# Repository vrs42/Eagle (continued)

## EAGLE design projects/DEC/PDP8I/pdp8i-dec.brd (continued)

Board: 2 copper layers, 330 parts (0 on the bottom side), 1704 nets, no tracks yet.

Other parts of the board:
U$1, U$2, U$3, U$4, U$5, U$6, U$7, U$8, U$9, U$10, U$11, U$12, U$13, U$14, U$15, U$16, U$17, U$18, U$19, U$20, U$21, U$22, U$23, U$24, U$25, U$26, U$27, U$28, U$29, U$30, U$31, U$32, U$33, U$34, U$35, U$36, U$37, U$38, U$39, U$40: CBLOCK

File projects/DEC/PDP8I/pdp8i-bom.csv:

"Qty";"Value";"Device";"Package";"Parts";"Description";"";
"2";"A607";"A607";"H807-2";"HJ24, HJ25";"A607 Digital to Analog Converter";"";
"28";"EMPTY";"EMPTY";"H807";"E03, E04, E05, E06, E07, E08, F04, F05, F06, F07, H06, H21, H22, H33, H35, H36, H37, H38, H39, H40, J21, J22, J35, J36, J37, J38, J39, J40";"Empty Slot";"";
"7";"G021";"G021";"H807";"A30, A31, A32, A33, B31, B32, B33";"Sense Amps";"";
"16";"G221";"G221";"H807";"C25, C26, C30, C31, C32, C33, C37, C38, D25, D26, D30, D31, D32, D33, D37, D38";"Memory Selector";"";
"9";"G228";"G228";"H807";"A27, A36, A37, B26, B27, B36, B37, C39, D39";"Inhibit Driver";"";
"2";"G610";"G610";"H807-2";"CD27, CD34";"G610 Core Connector";"";
"2";"G611";"G610";"H807-2";"CD29, CD36";"G610 Core Connector";"";
"7";"G624";"G624";"H807";"A25, A26, A38, A39, B25, B38, B39";"Resistor Board";"";
"1";"G792";"G792";"H807-2";"AB03";"Power Supply Connector";"";
"1";"G805";"G805";"H807-2";"AB01";"Negative Regulator";"";
"1";"G826";"G826";"H807-2";"AB02";"Regulator and Power Detector";"";
"4";"H807";"H807";"H807";"C28, C35, D28, D35";"Empty card slot";"";
"5";"M040";"M040";"H807";"C02, C03, C04, C05, C06";"M040 Solenoid Driver";"";
"40";"M113";"M113";"H807";"A05, A06, A11, A12, A13, A14, A15, A16, A17, A18, A19, B06, B08, B09, B21, C09, C10, C14, C15, C16, C17, C18, D07, D12, D13, D14, D15, D16, E09, E11, E12, E15, E22, E24, F20, F21, F22, F25, F29, F32";"10 2-input NAND Gates";"";
"17";"M115";"M115";"H807";"A20, B04, B07, B20, C11, C19, C20, C21, D09, D17, D18, D19, E14, E21, E25, F26, F28";"8 3-input NAND Gates";"";
"8";"M117";"M117";"H807";"D10, D20, D21, F11, F19, F23, F24, F27";"6 4-input NAND Gates";"";
"1";"M119";"M119";"H807";"F09";"3 8-input NAND Gates";"";
"8";"M160";"M160";"H807";"D23, E13, E26, E27, E28, E29, E30, F33";"AND-NOR Gates";"";
"4";"M162";"M162";"H807";"A07, A08, A09, A10";"Parity Circuit";"";
"6";"M216";"M206X";"H807";"B22, E18, E19, E20, E23, E33";"Two sets of 3 D flip-flops";"";
"10";"M216";"M216";"H807";"B05, B11, B17, B18, B19, C22, C23, C24, D11, D24";"Two sets of 3 D flip-flops";"";
"6";"M220";"M220";"H807-2";"EF34, EF35, EF36, EF37, EF38, EF39";"PDP-8 Major Registers";"";
"16";"M310";"M310";"H807";"A21, A22, A23, A24, C13, D06, D08, E16, E17, F12, F13, F14, F15, F16, F17, F18";"Tapped Delay Line";"";
"2";"M360";"M360";"H807";"B23, B24";"Variable Delay";"";
"1";"M401/M405/M501";"M501";"H807";"J30";"M401/M405/M501 Frequency Source";"";
"1";"M452";"M452";"H807";"F03";"M452 Baud Rate Clock";"";
"8";"M506";"M506";"H807";"J13, J14, J15, J16, J17, J18, J19, J20";"Hex Negative Bus Receiver";"";
"1";"M516";"M516";"H807";"D05";"Hex Positive Bus Receiver";"";
"12";"M617";"M617";"H807";"B12, B13, B14, B15, B16, B30, C12, D22, E31, E32, F30, F31";"6 4-input NAND Buffers";"";
"14";"M650";"M650";"H807";"H07, H08, H09, H10, H11, H12, H13, H14, H15, H16, H17, H18, H19, H20";"";"";
"2";"M660";"M660";"H807";"C08, F08";"Positive Level Driver";"";
"1";"M661";"M661";"H807";"C07";"Positive Level Driver";"";
"1";"M700";"M700";"H807-2";"EF10";"Manual Function Timing and Run";"";
"1";"M701";"M701";"H807-2";"HJ23";"M701 Display Control";"";
"1";"M703";"M703";"H807";"A04";"M703 Power Fail and Restart";"";
"1";"M704";"M704";"H807-2";"HJ29";"M704 Plotter Control";"";
"1";"M705";"M705";"H807-2";"HJ26";"Reader Control";"";
"1";"M706";"M706";"H807-2";"EF01";"M706 TTY Receiver";"";
"1";"M707";"M707";"H807-2";"EF02";"M707 TTY Transmitter";"";
"1";"M708";"M708";"H807";"H30";"M708 Clock Control";"";
"1";"M709";"M709";"H807-2";"HJ31";"M709 Clock Counter";"";
"1";"M710";"M710";"H807-2";"HJ28";"Punch Control";"";
"1";"M714";"M714";"H807";"J33";"M714 Card Reader Control";"";
"1";"M715";"M715";"H807-2";"HJ27";"Reader Clock";"";
"1";"M716";"M716";"H807-2";"HJ32";"M716 Card Reader Control";"";
"1";"M720";"M720";"H807";"B10";"M720 Memory Detection";"";
"4";"M900";"M916";"H807";"C40, D40, E40, F40";"Simple 36 pin connector/wire cable";"";
"17";"W011";"W011";"H807";"D04, H01, H02, H03, H04, H05, J01, J02, J03, J04, J05, J06, J07, J08, J09, J10, J11";"One-sided 9 pin connector/cable with grounds (Negibus).";"";
"3";"W023";"W023";"H807";"C01, D02, D03";"One-sided 18 pin connector/cable.";"";
"4";"W025";"W025";"H807-2";"AB28, AB29, AB34, AB35";"Core memory cable.";"";
"1";"W076";"W076";"H807";"J12";"W076 Terminal Connector";"";
"2";"W077";"M916";"H807";"A40, B40";"Simple 36 pin connector/wire cable";"";
"1";"W077";"W023";"H807";"D01";"One-sided 18 pin connector/cable.";"";
"1";"W991";"W991";"H807-2";"HJ34";"One-sided 36 pin (double hight) connector/cable.";"";

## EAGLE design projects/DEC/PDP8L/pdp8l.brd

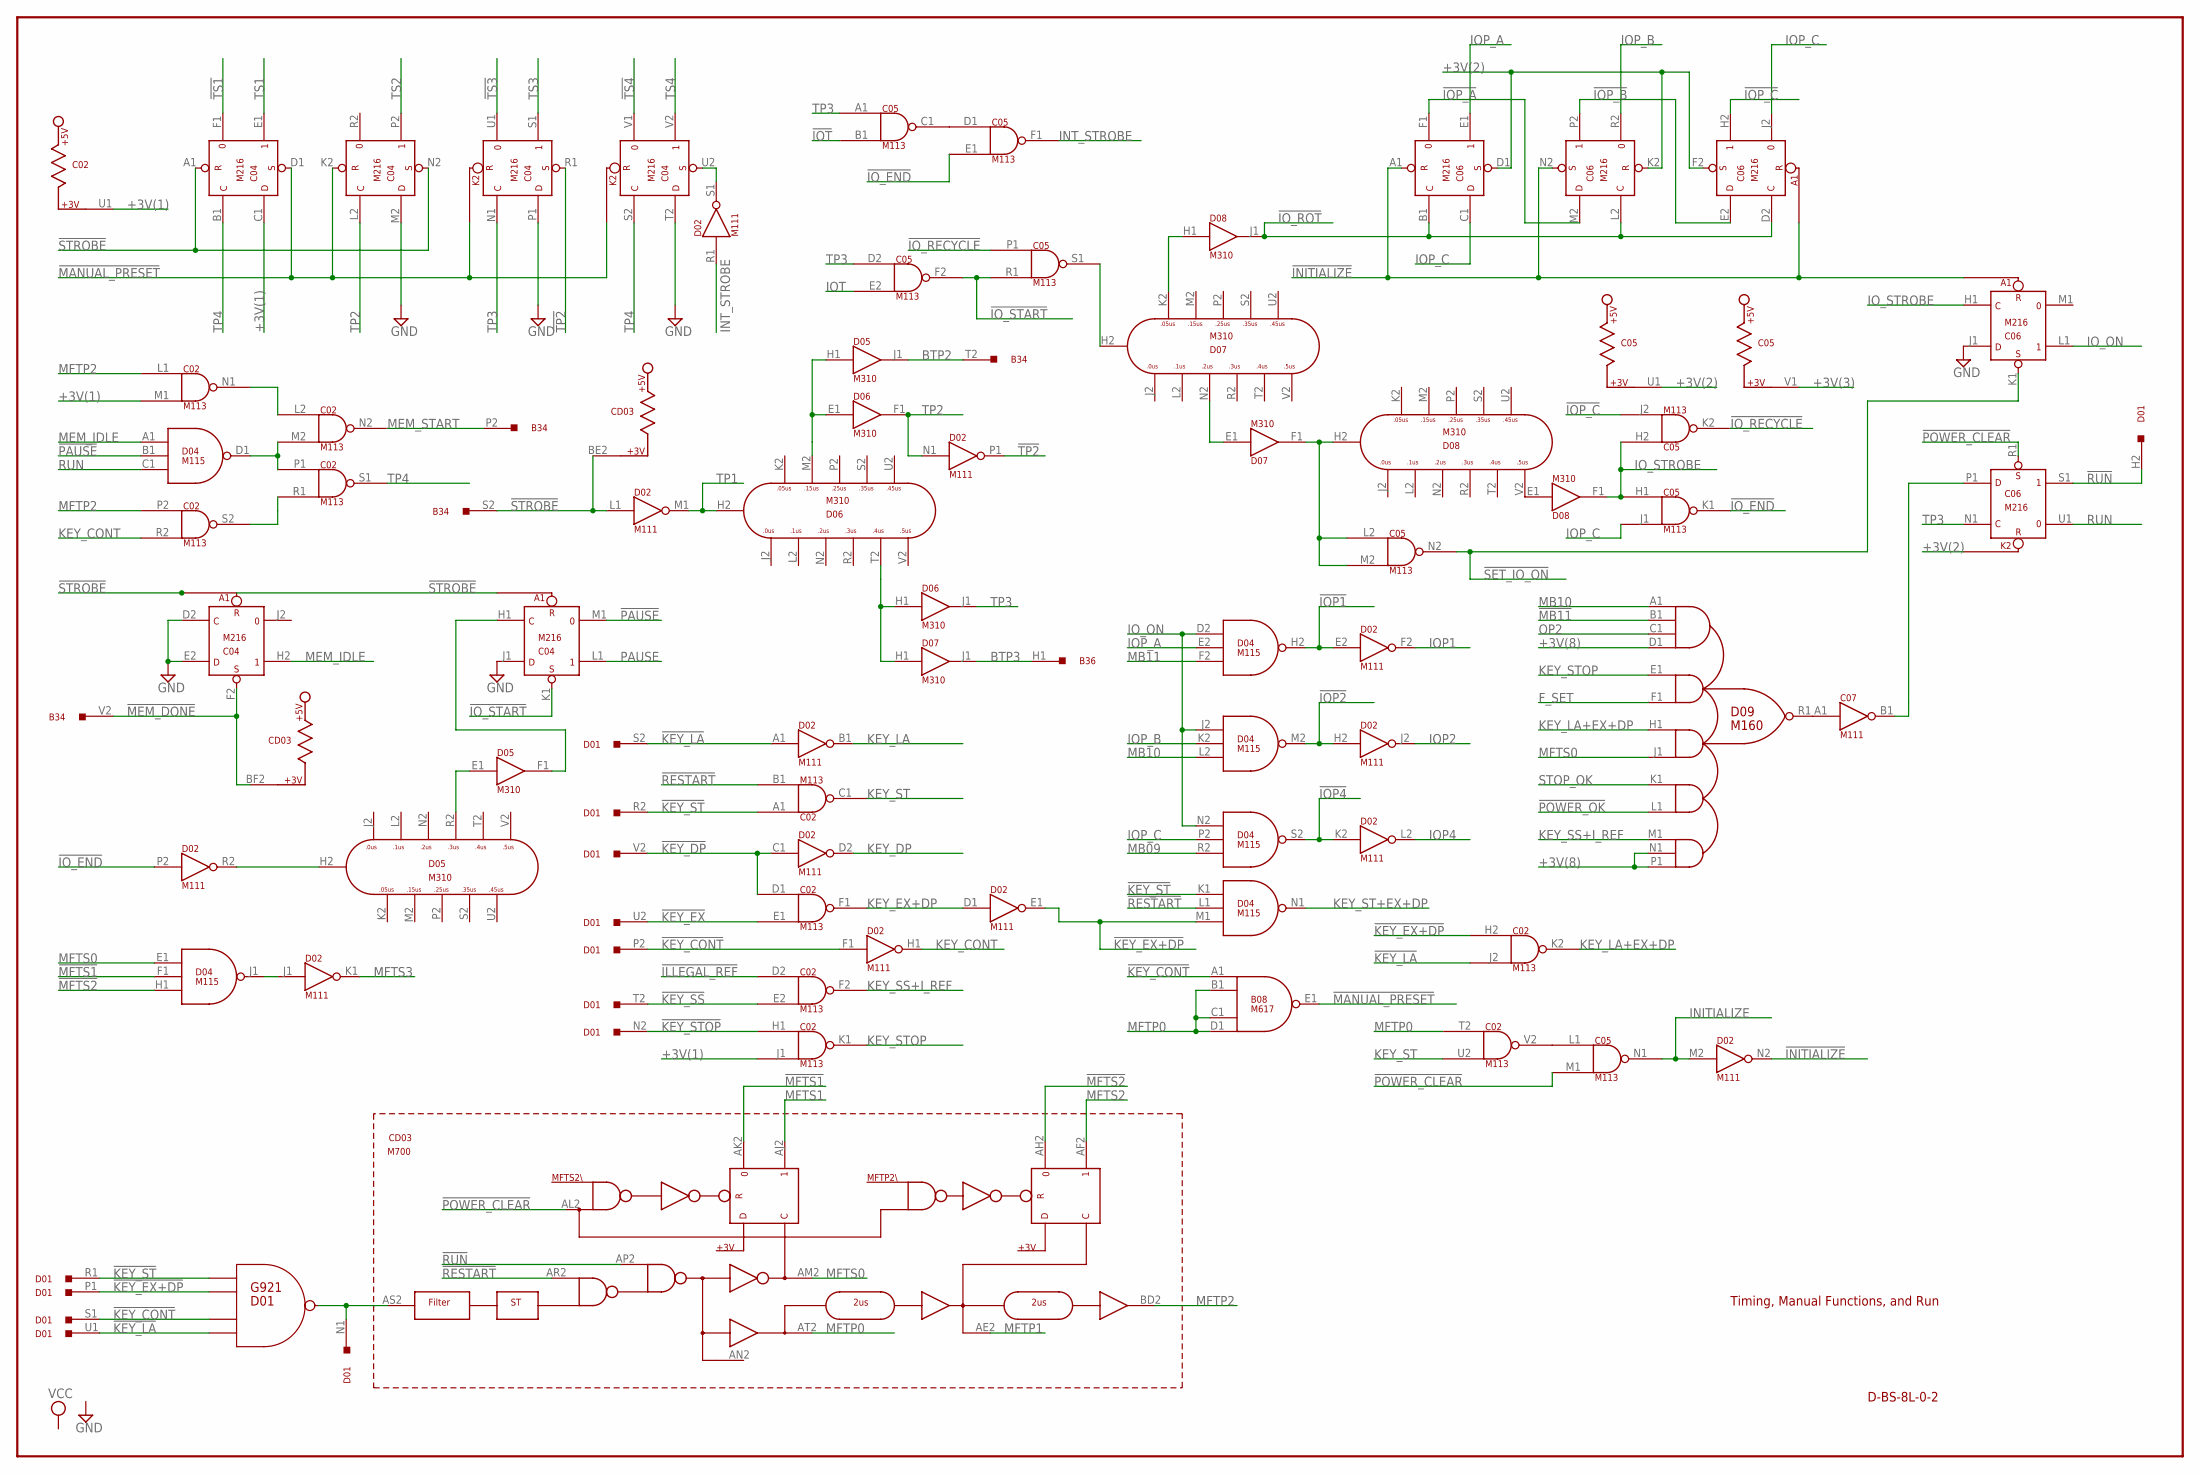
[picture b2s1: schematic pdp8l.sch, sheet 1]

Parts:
B08: M617; H807
B34, B36: M903; H807
C02, C05: M113; H807
C04, C06: M216; H807
C07: M111; H807
CD03: M700; H807-2
D01: G921; H807
D02: M111; H807
D04: M115; H807
D05, D06, D07, D08: M310; H807
D09: M160; H807

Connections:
!ILLEGAL_REF: C02.D2 (IN1); also elsewhere on the board
!INITIALIZE: C06.A1 (R), C06.N2 (S), D02.N2 (OUT); also elsewhere on the board
!INT_STROBE: C04.U2 (S), D02.S1 (OUT)
!IOP1: D02.E2 (IN), D04.H2 (OUT); also elsewhere on the board
!IOP2: D02.H2 (IN), D04.M2 (OUT); also elsewhere on the board
!IOP4: D02.K2 (IN), D04.S2 (OUT); also elsewhere on the board
!IOP_A: C06.F1 (0), C06.M2 (D)
!IOP_B: C06.E2 (D), C06.P2 (1)
!IOP_C: C05.J2 (IN2), C06.H2 (1)
!IOT: C05.B1 (IN2); also elsewhere on the board
!IO_END: C05.E1 (IN2), C05.K1 (OUT), D02.P2 (IN)
!IO_RECYCLE: C05.K2 (OUT), C05.P1 (IN1)
!IO_ROT: C06.B1 (C), C06.D2 (C), C06.L2 (C), D08.J1 (OUT)
!IO_START: C04.K1 (S), C05.F2 (OUT), C05.R1 (IN2)
!KEY_CONT: B08.A1 (IN1), D01.P2, D01.S1, D02.F1 (IN); also elsewhere on the board
!KEY_DP: C02.D1 (IN1), D01.V2, D02.C1 (IN)
!KEY_EX: C02.E1 (IN2), D01.U2
!KEY_EX+DP: C02.H2 (IN1), D01.P1, D02.E1 (OUT), D04.M1 (IN3)
!KEY_LA: C02.J2 (IN2), D01.S2, D01.U1, D02.A1 (IN); also elsewhere on the board
!KEY_SS: C02.E2 (IN2), D01.T2
!KEY_ST: C02.A1 (IN1), D01.R1, D01.R2, D04.K1 (IN1)
!KEY_STOP: C02.H1 (IN1), D01.N2
!MANUAL_PRESET: B08.E1 (OUT), C04.D1 (S), C04.K2 (R); also elsewhere on the board
!MB11: D09.B1 (IN1B); also elsewhere on the board
!MEM_DONE: B34.V2, C04.F2 (S), CD03.BF2; also elsewhere on the board
!MFTS1: CD03.AK2 (CK2), D04.F1 (IN2); also elsewhere on the board
!MFTS2: CD03.AH2 (CH2), D04.H1 (IN3); also elsewhere on the board
!MFTS3: D02.J1 (IN), D04.J1 (OUT)
!PAUSE: C04.M1 (0), D04.B1 (IN2)
!POWER_CLEAR: C05.M1 (IN2), C06.R1 (S), CD03.AL2 (CL2); also elsewhere on the board
!POWER_OK: D09.L1 (IN4B); also elsewhere on the board
!RESTART: C02.B1 (IN2), CD03.AR2 (CR2), D04.L1 (IN2); also elsewhere on the board
!RUN: C06.S1 (1), CD03.AP2 (CP2), D01.H2; also elsewhere on the board
!SET_IO_ON: C05.N2 (OUT), C06.K1 (S); also elsewhere on the board
!STROBE: B34.S2, C04.A1 (R), C04.N2 (S), CD03.BE2, D02.L1 (IN); also elsewhere on the board
!TP2: C04.R1 (S), D02.P1 (OUT); also elsewhere on the board
!TS1: C04.F1 (0); also elsewhere on the board
!TS3: C04.U1 (0); also elsewhere on the board
!TS4: C04.V1 (0); also elsewhere on the board
+3V(1): C02.J1 (IN2), C02.M1 (IN2), C02.U1, C04.C1 (D)
+3V(2): C05.U1, C06.D1 (S), C06.F2 (S), C06.K2 (R)
+3V(3): C05.V1; also elsewhere on the board
+3V(8): D09.D1 (IN1D), D09.N1 (IN5B), D09.P1 (IN5C); also elsewhere on the board
BTP2: B34.T2, D05.J1 (OUT)
BTP3: B36.H1, D07.J1 (OUT)
C02N1: C02.L2 (IN1), C02.N1 (OUT)
C02S2: C02.R1 (IN2), C02.S2 (OUT)
C02V2: C02.V2 (OUT), C05.L1 (IN1)
C05C1: C05.C1 (OUT), C05.D1 (IN1)
C05S1: C05.S1 (OUT), D07.H2
C07B1: C06.P1 (D), C07.B1 (OUT)
D01N1: CD03.AS2 (CS2), D01.N1
D04D1: C02.M2 (IN2), C02.P1 (IN1), D04.D1 (OUT)
D05F1: C04.H1 (C), D05.F1 (OUT)
D05R2: D05.E1 (IN), D05.R2
D06M2: D05.H1 (IN), D06.E1 (IN), D06.M2
D06T2: D06.H1 (IN), D06.T2, D07.H1 (IN)
D07K2: D07.K2, D08.H1 (IN)
D07N2: D07.E1 (IN), D07.N2
D08V2: D08.E1 (IN), D08.V2
D09R1: C07.A1 (IN), D09.R1 (OUT)
F_SET: D09.F1 (IN2B); also elsewhere on the board
GND: B08.C2 (GND), B08.T1 (GND), B34.A1 (GND), B34.C1 (GND), B34.C2 (GND), B34.F1 (GND), B34.F2 (GND), B34.J2 (GND), B34.K1 (GND), B34.L2 (GND), B34.N1 (GND), B34.N2 (GND), B34.R1 (GND), B34.R2 (GND), B34.T1 (GND), B34.U2 (GND), B36.A1 (GND), B36.C1 (GND), B36.C2 (GND), B36.F1 (GND), B36.F2 (GND), B36.J2 (GND), B36.K1 (GND), B36.L2 (GND), B36.N1 (GND), B36.N2 (GND), B36.R1 (GND), B36.R2 (GND), B36.T1 (GND), B36.U2 (GND), C02.C2 (GND), C02.T1 (GND), C04.C2 (GND), C04.D2 (C), C04.E2 (D), C04.J1 (D), C04.M2 (D), C04.P1 (D), C04.T1 (GND), C04.T2 (D), C05.C2 (GND), C05.T1 (GND), C06.C2 (GND), C06.J1 (D), C06.T1 (GND), C07.C2 (GND), C07.T1 (GND), CD03.AC2 (GND), CD03.BC2 (GND), D02.C2 (GND), D02.T1 (GND), D04.C2 (GND), D04.T1 (GND), D05.C2 (GND), D05.T1 (GND), D06.C2 (GND), D06.T1 (GND), D07.C2 (GND), D07.T1 (GND), D08.C2 (GND), D08.T1 (GND), D09.C2 (GND), D09.T1 (GND); also elsewhere on the board
INITIALIZE: C05.N1 (OUT), D02.M2 (IN); also elsewhere on the board
INT_STROBE: C05.F1 (OUT), D02.R1 (IN); also elsewhere on the board
IOP1: D02.F2 (OUT); also elsewhere on the board
IOP2: D02.J2 (OUT); also elsewhere on the board
IOP4: D02.L2 (OUT); also elsewhere on the board
IOP_A: C06.E1 (1), D04.E2 (IN2)
IOP_B: C06.R2 (0), D04.K2 (IN2)
IOP_C: C05.J1 (IN2), C06.C1 (D), C06.J2 (0), D04.P2 (IN2)
IOT: C05.E2 (IN2); also elsewhere on the board
IO_END: D02.R2 (OUT), D05.H2
IO_ON: C06.L1 (1), D04.D2 (IN1), D04.J2 (IN1), D04.N2 (IN1)
IO_STROBE: C05.H1 (IN1), C05.H2 (IN1), C06.H1 (C), D08.F1 (OUT); also elsewhere on the board
KEY_CONT: C02.R2 (IN2), D02.H1 (OUT)
KEY_DP: D02.D2 (OUT); also elsewhere on the board
KEY_EX+DP: C02.F1 (OUT), D02.D1 (IN); also elsewhere on the board
KEY_LA: D02.B1 (OUT); also elsewhere on the board
KEY_LA+EX+DP: C02.K2 (OUT), D09.H1 (IN3A); also elsewhere on the board
KEY_SS+I_REF: C02.F2 (OUT), D09.M1 (IN5A)
KEY_ST: C02.C1 (OUT), C02.U2 (IN2); also elsewhere on the board
KEY_ST+EX+DP: D04.N1 (OUT); also elsewhere on the board
KEY_STOP: C02.K1 (OUT), D09.E1 (IN2A)
MB09: D04.R2 (IN3); also elsewhere on the board
MB10: D04.L2 (IN3), D09.A1 (IN1A); also elsewhere on the board
MB11: D04.F2 (IN3); also elsewhere on the board
MEM_IDLE: C04.H2 (1), D04.A1 (IN1)
MEM_START: B34.P2, C02.N2 (OUT); also elsewhere on the board
MFTP0: B08.B1 (IN2), B08.C1 (IN3), B08.D1 (IN4), C02.T2 (IN1), CD03.AT2 (CT2); also elsewhere on the board
MFTP1: CD03.AE2 (CE2); also elsewhere on the board
MFTP2: C02.L1 (IN1), C02.P2 (IN1), CD03.BD2 (DD2); also elsewhere on the board
MFTS0: CD03.AM2 (CM2), D04.E1 (IN1), D09.J1 (IN3B)
MFTS1: CD03.AJ2 (CJ2); also elsewhere on the board
MFTS2: CD03.AF2 (CF2); also elsewhere on the board
MFTS3: D02.K1 (OUT); also elsewhere on the board
OP2: D09.C1 (IN1C); also elsewhere on the board
PAUSE: C04.L1 (1); also elsewhere on the board
RUN: C06.U1 (0), D04.C1 (IN3)
SET_IO_ON: C05.L2 (IN1), C05.M2 (IN2), D07.F1 (OUT), D08.H2
STOP_OK: D09.K1 (IN4A); also elsewhere on the board
TP1: D02.M1 (OUT), D06.H2; also elsewhere on the board
TP2: C04.L2 (C), D02.N1 (IN), D06.F1 (OUT); also elsewhere on the board
TP3: C04.N1 (C), C05.A1 (IN1), C05.D2 (IN1), C06.N1 (C), D06.J1 (OUT); also elsewhere on the board
TP4: C02.S1 (OUT), C04.B1 (C), C04.S2 (C); also elsewhere on the board
TS1: C04.E1 (1); also elsewhere on the board
TS2: C04.P2 (1); also elsewhere on the board
TS3: C04.S1 (1); also elsewhere on the board
TS4: C04.V2 (1); also elsewhere on the board
VCC: B08.A2 (VCC), C02.A2 (VCC), C04.A2 (VCC), C05.A2 (VCC), C06.A2 (VCC), C07.A2 (VCC), CD03.AA2 (VCC), CD03.BA2 (VCC), D02.A2 (VCC), D04.A2 (VCC), D05.A2 (VCC), D06.A2 (VCC), D07.A2 (VCC), D08.A2 (VCC), D09.A2 (VCC); also elsewhere on the board

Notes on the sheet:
G921
D01
D-BS-8L-0-2
Timing, Manual Functions, and Run

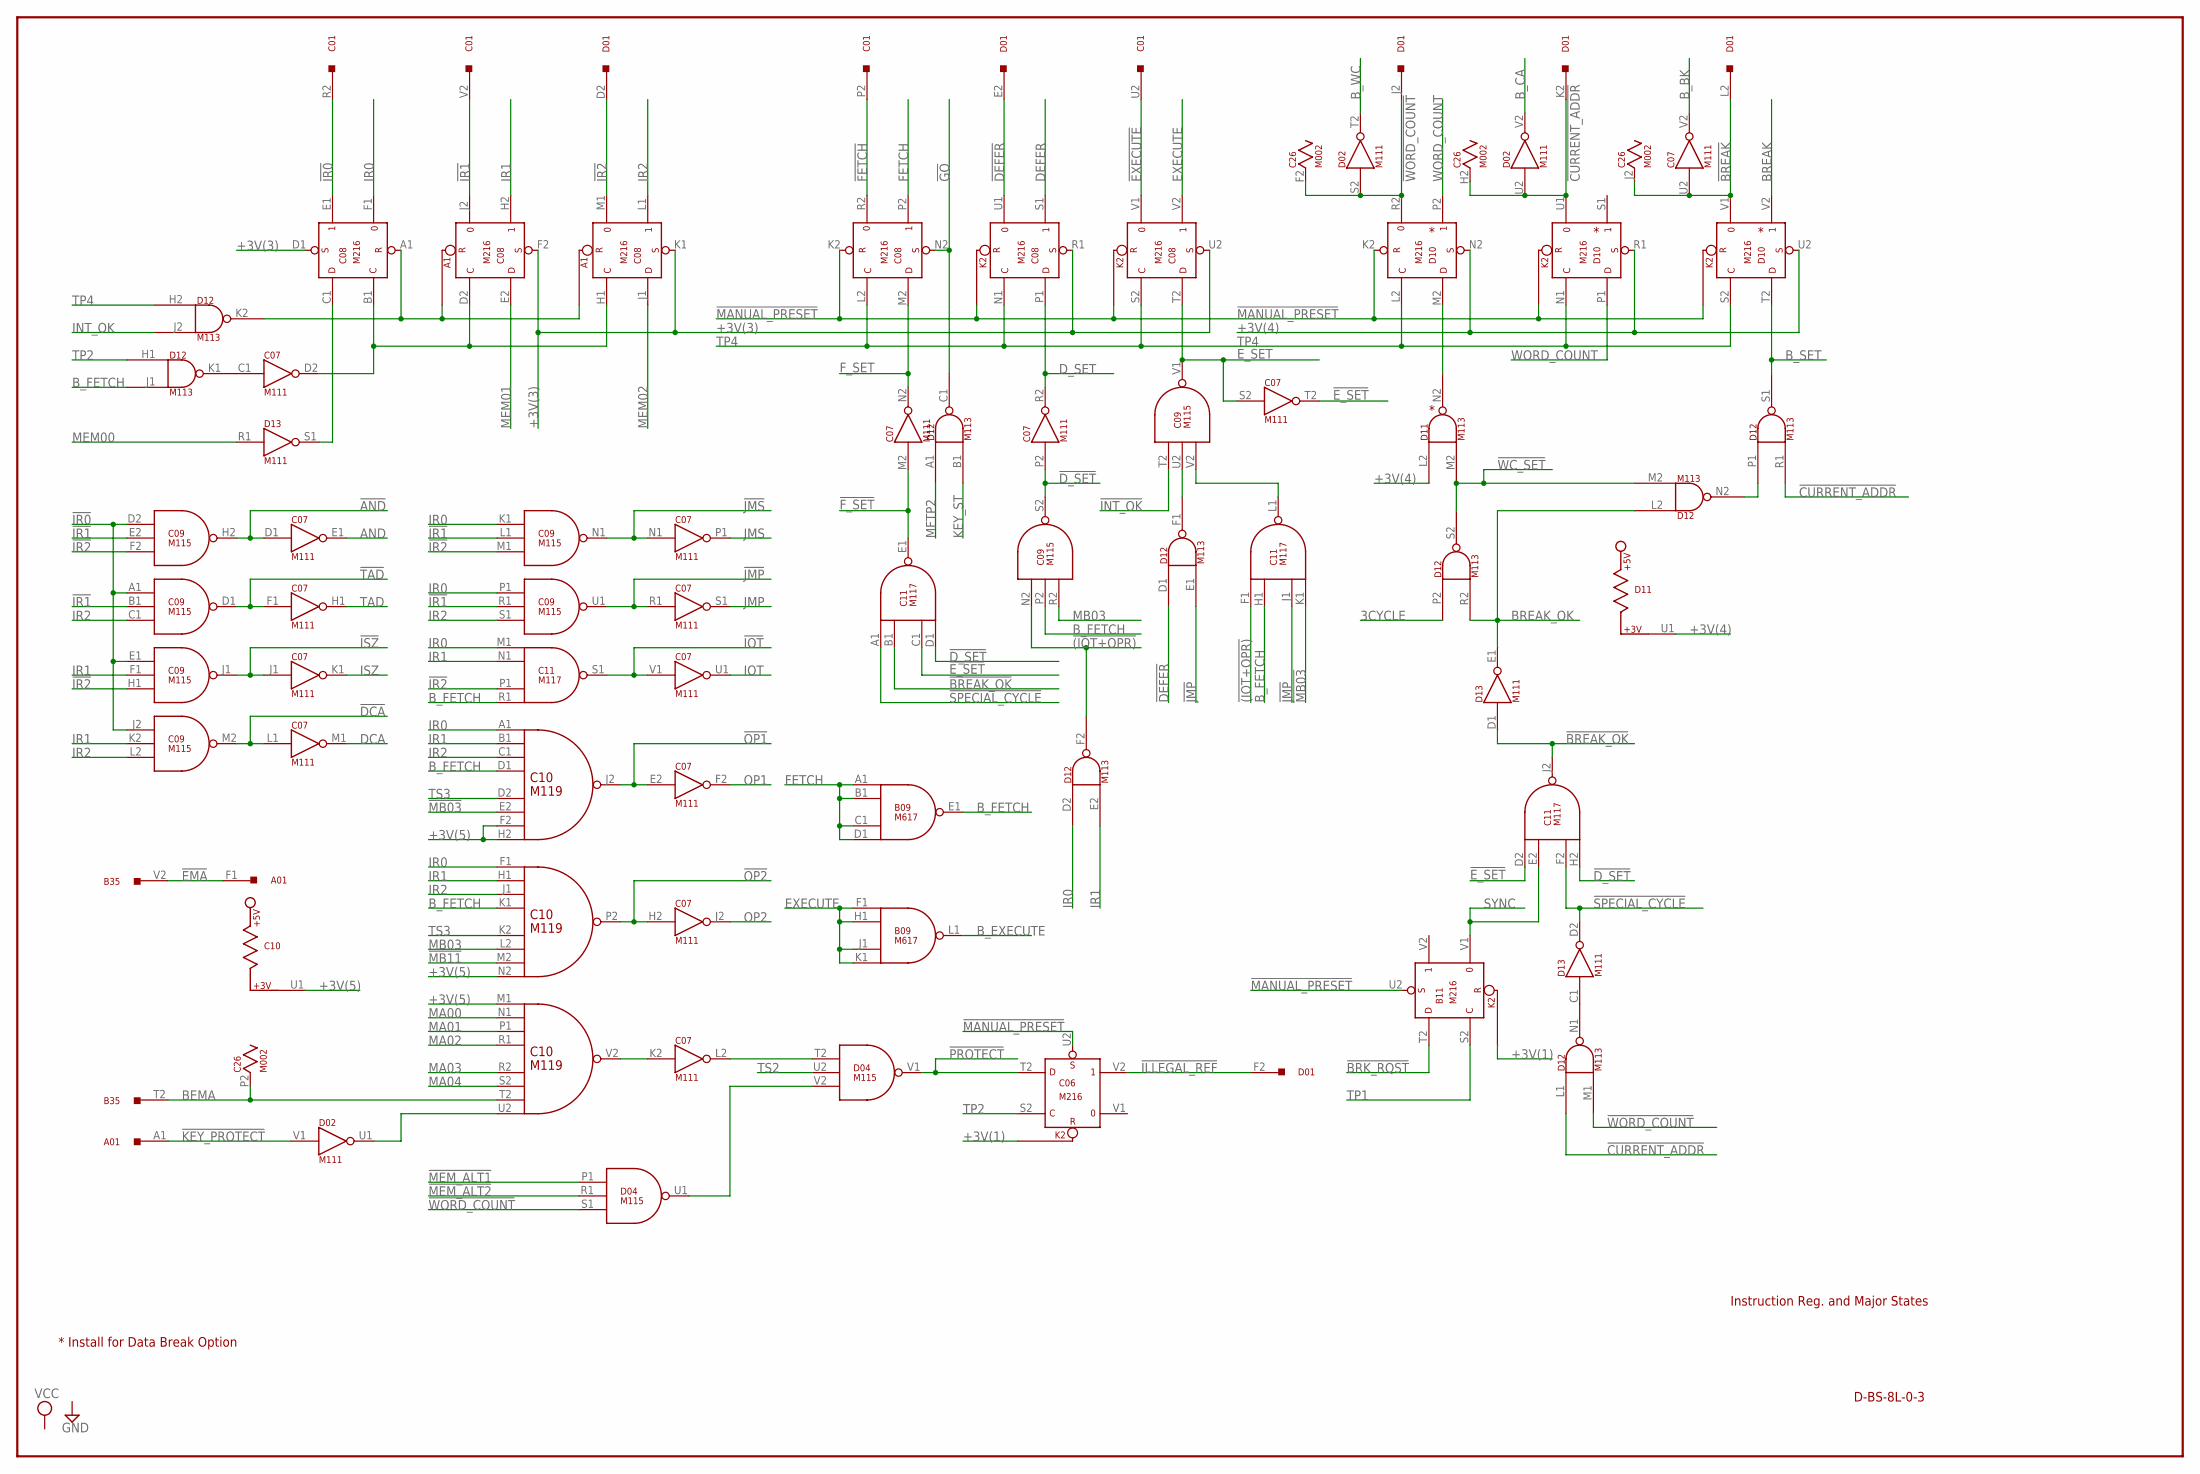
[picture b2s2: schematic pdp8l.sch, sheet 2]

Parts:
A01: G921; H807
B09: M617; H807
B11: M216; H807
B35: M903; H807
C01: G921; H807
C06, C08: M216; H807
C07: M111; H807
C09: M115; H807
C10: M119; H807
C11: M117; H807
C26: M002; H807
D01: G921; H807
D02, D13: M111; H807
D04: M115; H807
D10: M216; H807
D11, D12: M113; H807

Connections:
3CYCLE: D12.P2 (IN1); also elsewhere on the board
!(IOT+OPR): C09.N2 (IN1), C11.F1 (IN1), D12.F2 (OUT)
!AND: C07.D1 (IN), C09.H2 (OUT); also elsewhere on the board
!BREAK: C07.U2 (IN), C26.J2, D01.L2, D10.V1 (0); also elsewhere on the board
!BREAK_OK: C11.B1 (IN2), C11.J2 (OUT), D13.D1 (IN); also elsewhere on the board
!BRK_RQST: B11.T2 (D); also elsewhere on the board
!CURRENT_ADDR: C26.H2, D01.K2, D02.U2 (IN), D10.U1 (0), D12.L1 (IN1), D12.R1 (IN2)
!DCA: C07.L1 (IN), C09.M2 (OUT); also elsewhere on the board
!DEFER: C08.U1 (0), D01.E2, D12.D1 (IN1)
!D_SET: C07.P2 (IN), C09.S2 (OUT), C11.D1 (IN4), C11.H2 (IN4); also elsewhere on the board
!EMA: A01.F1, B35.V2
!EXECUTE: C01.U2, C08.V1 (0)
!E_SET: C07.T2 (OUT), C11.C1 (IN3), C11.D2 (IN1); also elsewhere on the board
!FETCH: C01.P2, C08.R2 (0)
!F_SET: C07.M2 (IN), C11.E1 (OUT); also elsewhere on the board
!GO: C08.N2 (S), D12.C1 (OUT); also elsewhere on the board
!ILLEGAL_REF: C06.V2 (1), D01.F2; also elsewhere on the board
!INT_OK: C09.T2 (IN1); also elsewhere on the board
!IOT: C07.V1 (IN), C11.S1 (OUT); also elsewhere on the board
!IR0: C01.R2, C08.E1 (1), C09.A1 (IN1), C09.D2 (IN1), C09.E1 (IN1), C09.J2 (IN1); also elsewhere on the board
!IR1: C01.V2, C08.J2 (0), C09.B1 (IN2), C09.E2 (IN2), C09.L1 (IN2), C09.R1 (IN2)
!IR2: C08.M1 (0), C09.F2 (IN3), C09.H1 (IN3), C09.M1 (IN3), C11.P1 (IN3), D01.D2
!ISZ: C07.J1 (IN), C09.J1 (OUT)
!JMP: C07.R1 (IN), C09.U1 (OUT), C11.J1 (IN3), D12.E1 (IN2); also elsewhere on the board
!JMS: C07.N1 (IN), C09.N1 (OUT); also elsewhere on the board
!KEY_PROTECT: A01.A1, D02.V1 (IN)
!MANUAL_PRESET: B11.U2 (S), C06.U2 (S), C08.K2 (R), D10.K2 (R); also elsewhere on the board
!MB03: C10.E2 (IN6), C11.K1 (IN4); also elsewhere on the board
!MB11: C10.M2 (IN7); also elsewhere on the board
!MEM_ALT1: D04.P1 (IN1); also elsewhere on the board
!MEM_ALT2: D04.R1 (IN2); also elsewhere on the board
!OP1: C07.E2 (IN), C10.J2 (OUT); also elsewhere on the board
!OP2: C07.H2 (IN), C10.P2 (OUT); also elsewhere on the board
!PROTECT: C06.T2 (D), D04.V1 (OUT); also elsewhere on the board
!SPECIAL_CYCLE: C11.A1 (IN1), C11.F2 (IN3), D13.D2 (OUT)
!TAD: C07.F1 (IN), C09.D1 (OUT); also elsewhere on the board
!WC_SET: D11.M2 (IN2), D12.M2 (IN2), D12.S2 (OUT); also elsewhere on the board
!WORD_COUNT: C26.F2, D01.J2, D02.S2 (IN), D04.S1 (IN3), D10.R2 (0), D12.M1 (IN2); also elsewhere on the board
+3V(3): C08.D1 (S), C08.F2 (S), C08.K1 (S), C08.R1 (S), C08.U2 (S); also elsewhere on the board
+3V(4): D10.N2 (S), D10.R1 (S), D10.U2 (S), D11.L2 (IN1), D11.U1; also elsewhere on the board
+3V(5): C10.F2 (IN7), C10.H2 (IN8), C10.M1 (IN1), C10.N2 (IN8), C10.U1
AND: C07.E1 (OUT); also elsewhere on the board
BEMA: B35.T2, C10.T2 (IN7), C26.P2
BREAK: D10.V2 (1); also elsewhere on the board
BREAK_OK: D12.L2 (IN1), D12.R2 (IN2), D13.E1 (OUT); also elsewhere on the board
B_BK: C07.V2 (OUT); also elsewhere on the board
B_CA: D02.V2 (OUT); also elsewhere on the board
B_EXECUTE: B09.L1 (OUT); also elsewhere on the board
B_FETCH: B09.E1 (OUT), C09.P2 (IN2), C10.D1 (IN4), C10.K1 (IN4), C11.H1 (IN2), C11.R1 (IN4), D12.J1 (IN2); also elsewhere on the board
B_SET: D10.T2 (D), D12.S1 (OUT); also elsewhere on the board
B_WC: D02.T2 (OUT); also elsewhere on the board
C07D2: C07.D2 (OUT), C08.B1 (C), C08.D2 (C), C08.H1 (C)
C07L2: C07.L2 (OUT), D04.T2 (IN1)
C10V2: C07.K2 (IN), C10.V2 (OUT)
C11L1: C09.V2 (IN3), C11.L1 (OUT)
D04U1: D04.U1 (OUT), D04.V2 (IN3)
D11N2: D10.M2 (D), D11.N2 (OUT)
D12F1: C09.U2 (IN2), D12.F1 (OUT)
D12K1: C07.C1 (IN), D12.K1 (OUT)
D12K2: C08.A1 (R), D12.K2 (OUT)
D12N2: D12.N2 (OUT), D12.P1 (IN1)
D13S1: C08.C1 (D), D13.S1 (OUT)
DCA: C07.M1 (OUT); also elsewhere on the board
DEFER: C08.S1 (1); also elsewhere on the board
D_SET: C07.R2 (OUT), C08.P1 (D)
EXECUTE: B09.F1 (IN1), B09.H1 (IN2), B09.J1 (IN3), B09.K1 (IN4), C08.V2 (1)
E_SET: C07.S2 (IN), C08.T2 (D), C09.V1 (OUT)
FETCH: B09.A1 (IN1), B09.B1 (IN2), B09.C1 (IN3), B09.D1 (IN4), C08.P2 (1); also elsewhere on the board
F_SET: C07.N2 (OUT), C08.M2 (D); also elsewhere on the board
GND: B09.C2 (GND), B09.T1 (GND), B11.C2 (GND), B11.T1 (GND), B35.A1 (GND), B35.C1 (GND), B35.C2 (GND), B35.F1 (GND), B35.F2 (GND), B35.J2 (GND), B35.K1 (GND), B35.L2 (GND), B35.N1 (GND), B35.N2 (GND), B35.R1 (GND), B35.R2 (GND), B35.T1 (GND), B35.U2 (GND), C06.C2 (GND), C06.T1 (GND), C07.C2 (GND), C07.T1 (GND), C08.C2 (GND), C08.T1 (GND), C09.C2 (GND), C09.T1 (GND), C10.C2 (GND), C10.T1 (GND), C11.C2 (GND), C11.T1 (GND), C26.C2 (GND), D02.C2 (GND), D02.T1 (GND), D04.C2 (GND), D04.T1 (GND), D10.C2 (GND), D10.T1 (GND), D11.C2 (GND), D11.T1 (GND), D12.C2 (GND), D12.T1 (GND), D13.C2 (GND), D13.T1 (GND); also elsewhere on the board
INT_OK: D12.J2 (IN2); also elsewhere on the board
IOT: C07.U1 (OUT); also elsewhere on the board
IR0: C08.F1 (0), C09.K1 (IN1), C09.P1 (IN1), C10.A1 (IN1), C10.F1 (IN1), C11.M1 (IN1), D12.D2 (IN1)
IR1: C08.H2 (1), C09.F1 (IN2), C09.K2 (IN2), C10.B1 (IN2), C10.H1 (IN2), C11.N1 (IN2), D12.E2 (IN2)
IR2: C08.L1 (1), C09.C1 (IN3), C09.L2 (IN3), C09.S1 (IN3), C10.C1 (IN3), C10.J1 (IN3)
ISZ: C07.K1 (OUT); also elsewhere on the board
JMP: C07.S1 (OUT); also elsewhere on the board
JMS: C07.P1 (OUT); also elsewhere on the board
KEY_PROTECT: C10.U2 (IN8), D02.U1 (OUT)
KEY_ST: D12.B1 (IN2); also elsewhere on the board
MA00: C10.N1 (IN2); also elsewhere on the board
MA01: C10.P1 (IN3); also elsewhere on the board
MA02: C10.R1 (IN4); also elsewhere on the board
MA03: C10.R2 (IN5); also elsewhere on the board
MA04: C10.S2 (IN6); also elsewhere on the board
MB03: C09.R2 (IN3), C10.L2 (IN6); also elsewhere on the board
MEM00: D13.R1 (IN); also elsewhere on the board
MEM01: C08.E2 (D); also elsewhere on the board
MEM02: C08.J1 (D); also elsewhere on the board
MFTP2: D12.A1 (IN1); also elsewhere on the board
OP1: C07.F2 (OUT); also elsewhere on the board
OP2: C07.J2 (OUT); also elsewhere on the board
SPECIAL_CYCLE: D12.N1 (OUT), D13.C1 (IN)
SYNC: B11.V1 (0), C11.E2 (IN2)
TAD: C07.H1 (OUT); also elsewhere on the board
TP1: B11.S2 (C); also elsewhere on the board
TP2: C06.S2 (C), D12.H1 (IN1); also elsewhere on the board
TP4: C08.L2 (C), C08.N1 (C), C08.S2 (C), D10.L2 (C), D10.N1 (C), D10.S2 (C), D12.H2 (IN1); also elsewhere on the board
TS2: D04.U2 (IN2); also elsewhere on the board
TS3: C10.D2 (IN5), C10.K2 (IN5); also elsewhere on the board
VCC: B09.A2 (VCC), B11.A2 (VCC), C06.A2 (VCC), C07.A2 (VCC), C08.A2 (VCC), C09.A2 (VCC), C10.A2 (VCC), C11.A2 (VCC), C26.A2 (VCC), D02.A2 (VCC), D04.A2 (VCC), D10.A2 (VCC), D11.A2 (VCC), D12.A2 (VCC), D13.A2 (VCC); also elsewhere on the board
WORD_COUNT: D10.P1 (D), D10.P2 (1)

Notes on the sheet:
D-BS-8L-0-3
Instruction Reg. and Major States
* Install for Data Break Option
